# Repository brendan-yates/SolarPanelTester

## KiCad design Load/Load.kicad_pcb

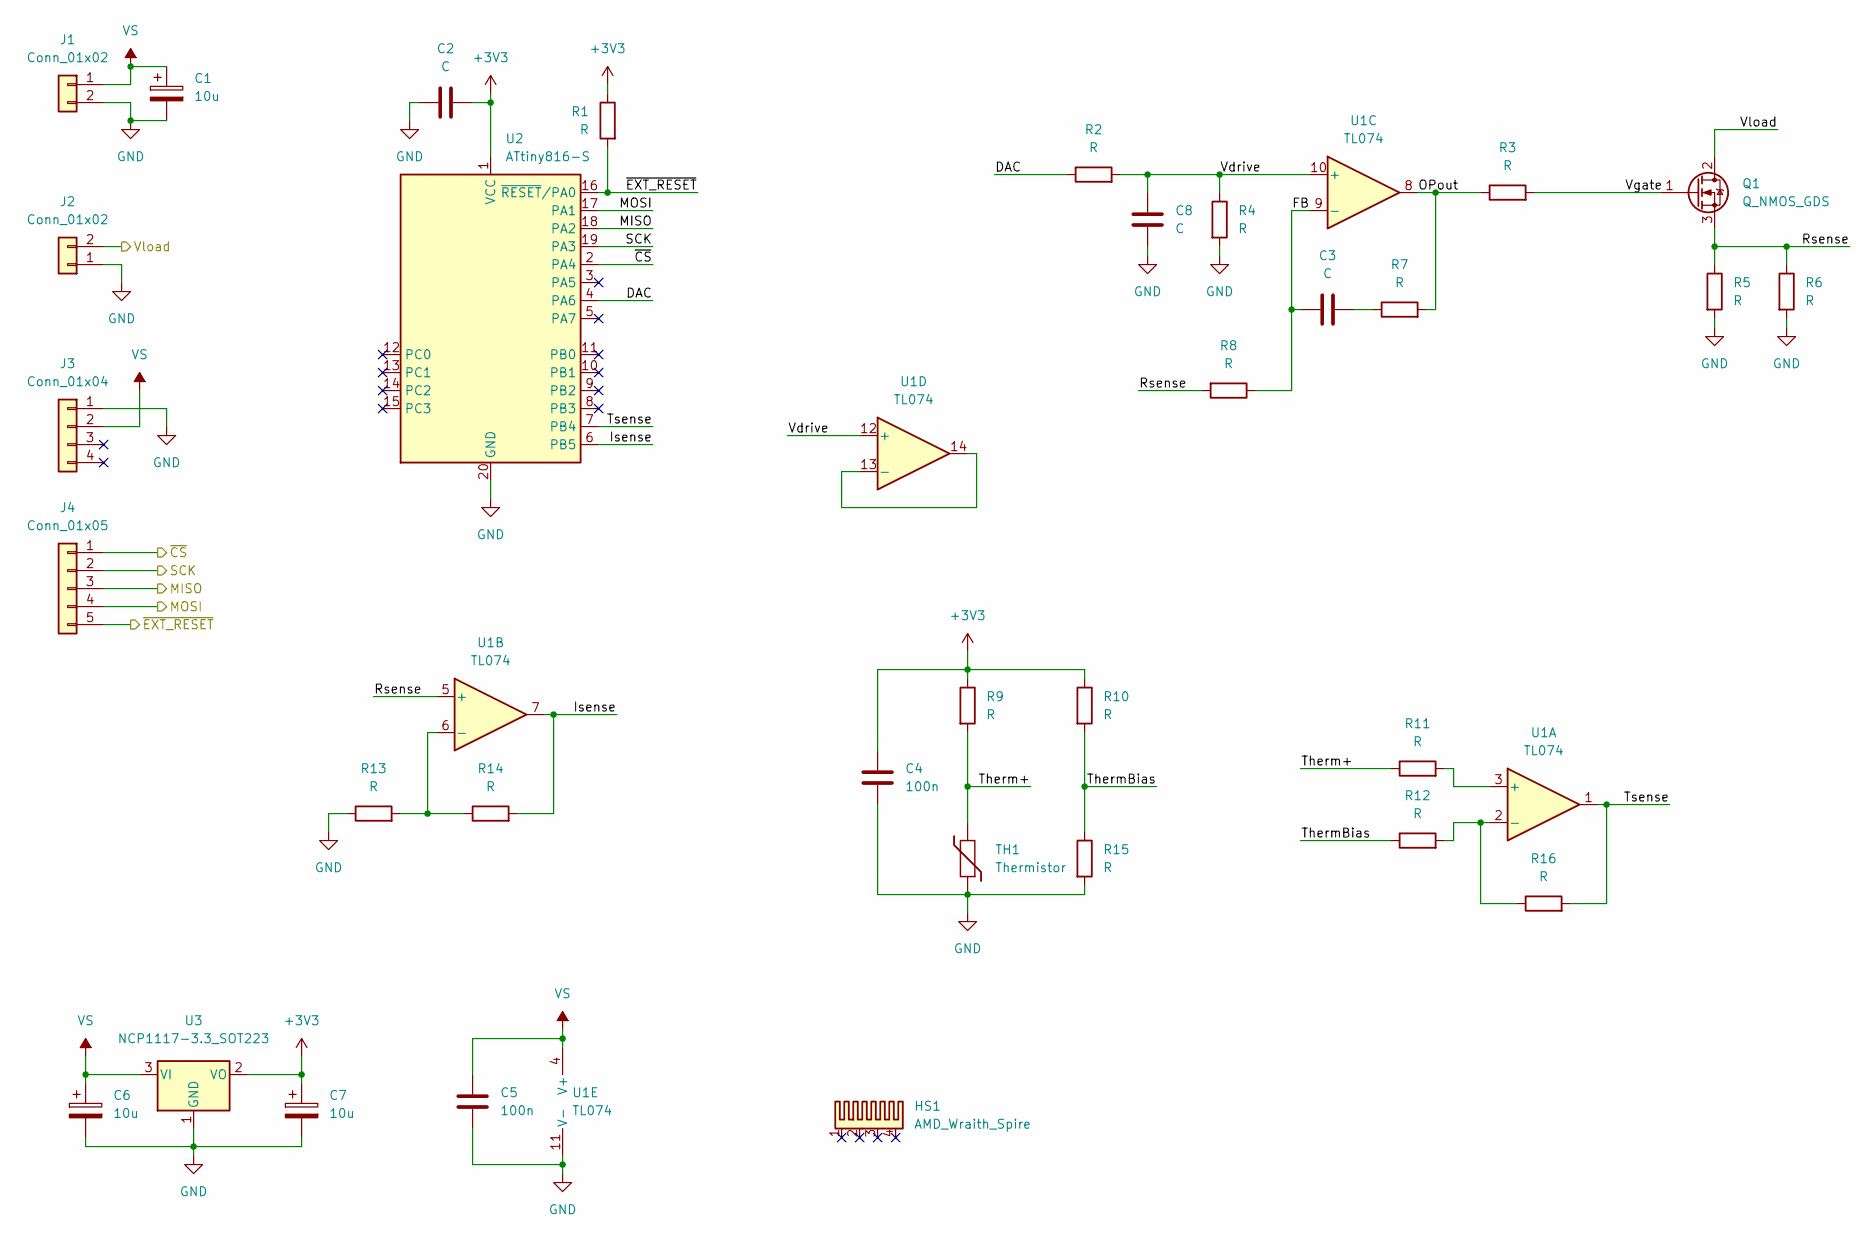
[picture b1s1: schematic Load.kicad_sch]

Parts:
C1, C6, C7: 10u; CP_EIA-3216-10_Kemet-I_Pad1.58x1.35mm_HandSolder
C2, C3, C8: C; C_0805_2012Metric_Pad1.18x1.45mm_HandSolder
C4, C5: 100n; C_0805_2012Metric_Pad1.18x1.45mm_HandSolder
HS1: AMD_Wraith_Spire
J1: Conn_01x02; PinSocket_1x02_P2.54mm_Vertical
J2: Conn_01x02; SolderWire-1sqmm_1x02_P5.4mm_D1.4mm_OD2.7mm_Relief
J3: Conn_01x04; PinSocket_1x04_P2.54mm_Vertical
J4: Conn_01x05; PinHeader_1x05_P2.54mm_Horizontal
Q1: Q_NMOS_GDS; TO-268-2
R1, R2, R3, R4, R7, R8, R9, R10, R11, R12, R13, R14, R15, R16: R; R_0805_2012Metric_Pad1.20x1.40mm_HandSolder
R5, R6: R; R_2512_6332Metric_Pad1.40x3.35mm_HandSolder
TH1: Thermistor; PinHeader_1x02_P2.54mm_Horizontal
U1: TL074; SOIC-14_3.9x8.7mm_P1.27mm
U2: ATtiny816-S; SOIC-20W_7.5x12.8mm_P1.27mm
U3: NCP1117-3.3_SOT223; SOT-223-3_TabPin2

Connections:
+3V3: C2.2, C4.2, C7.1, R1.1, R9.1, R10.1, U2.1 (VCC), U3.2 (VO)
/DAC: R2.1, U2.4 (PA6)
/FB: C3.1, R8.1, U1.9 (-)
/Isense: R14.2, U1.7, U2.6 (PB5)
/MISO: J4.3, U2.18 (PA2)
/MOSI: J4.4, U2.17 (PA1)
/OPout: R3.1, R7.2, U1.8
/Rsense: Q1.3 (S), R5.1, R6.1, R8.2, U1.5 (+)
/SCK: J4.2, U2.19 (PA3)
/Therm+: R9.2, R11.1, TH1.2
/ThermBias: R10.2, R12.1, R15.1
/Tsense: R16.2, U1.1, U2.7 (PB4)
/Vdrive: C8.2, R2.2, R4.1, U1.10 (+), U1.12 (+)
/Vgate: Q1.1 (G), R3.2
/Vload: J2.2, Q1.2 (D)
/~CS: J4.1, U2.2 (PA4)
/~EXT_RESET: J4.5, R1.2, U2.16 (~RESET/PA0)
GND: C1.2, C2.1, C4.1, C5.1, C6.2, C7.2, C8.1, J1.2, J2.1, J3.1, R4.2, R5.2, R6.2, R13.1, R15.2, TH1.1, U1.11 (V-), U2.20 (GND), U3.1 (GND)
unnamed: C3.2, R7.1
unnamed: R11.2, U1.3 (+)
unnamed: R12.2, R16.1, U1.2 (-)
unnamed: R13.2, R14.1, U1.6 (-)
unnamed: U1.13 (-), U1.14
VS: C1.1, C5.2, C6.1, J1.1, J3.2, U1.4 (V+), U3.3 (VI)

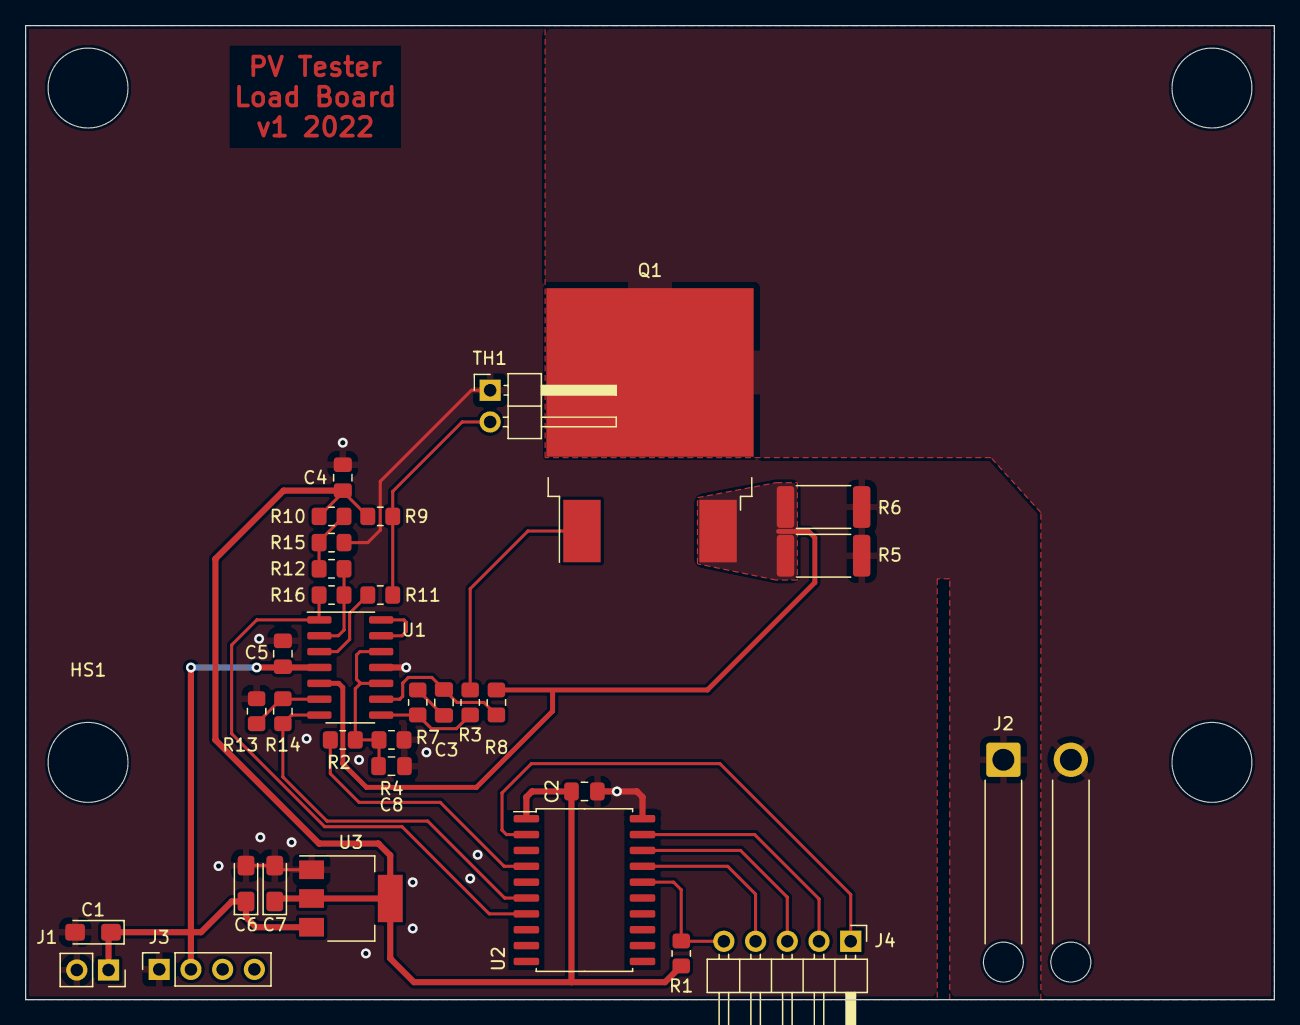
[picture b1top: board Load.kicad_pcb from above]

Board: 2 copper layers, 100.0 x 78.0 mm, 34 parts (0 on the bottom side), 24 nets.

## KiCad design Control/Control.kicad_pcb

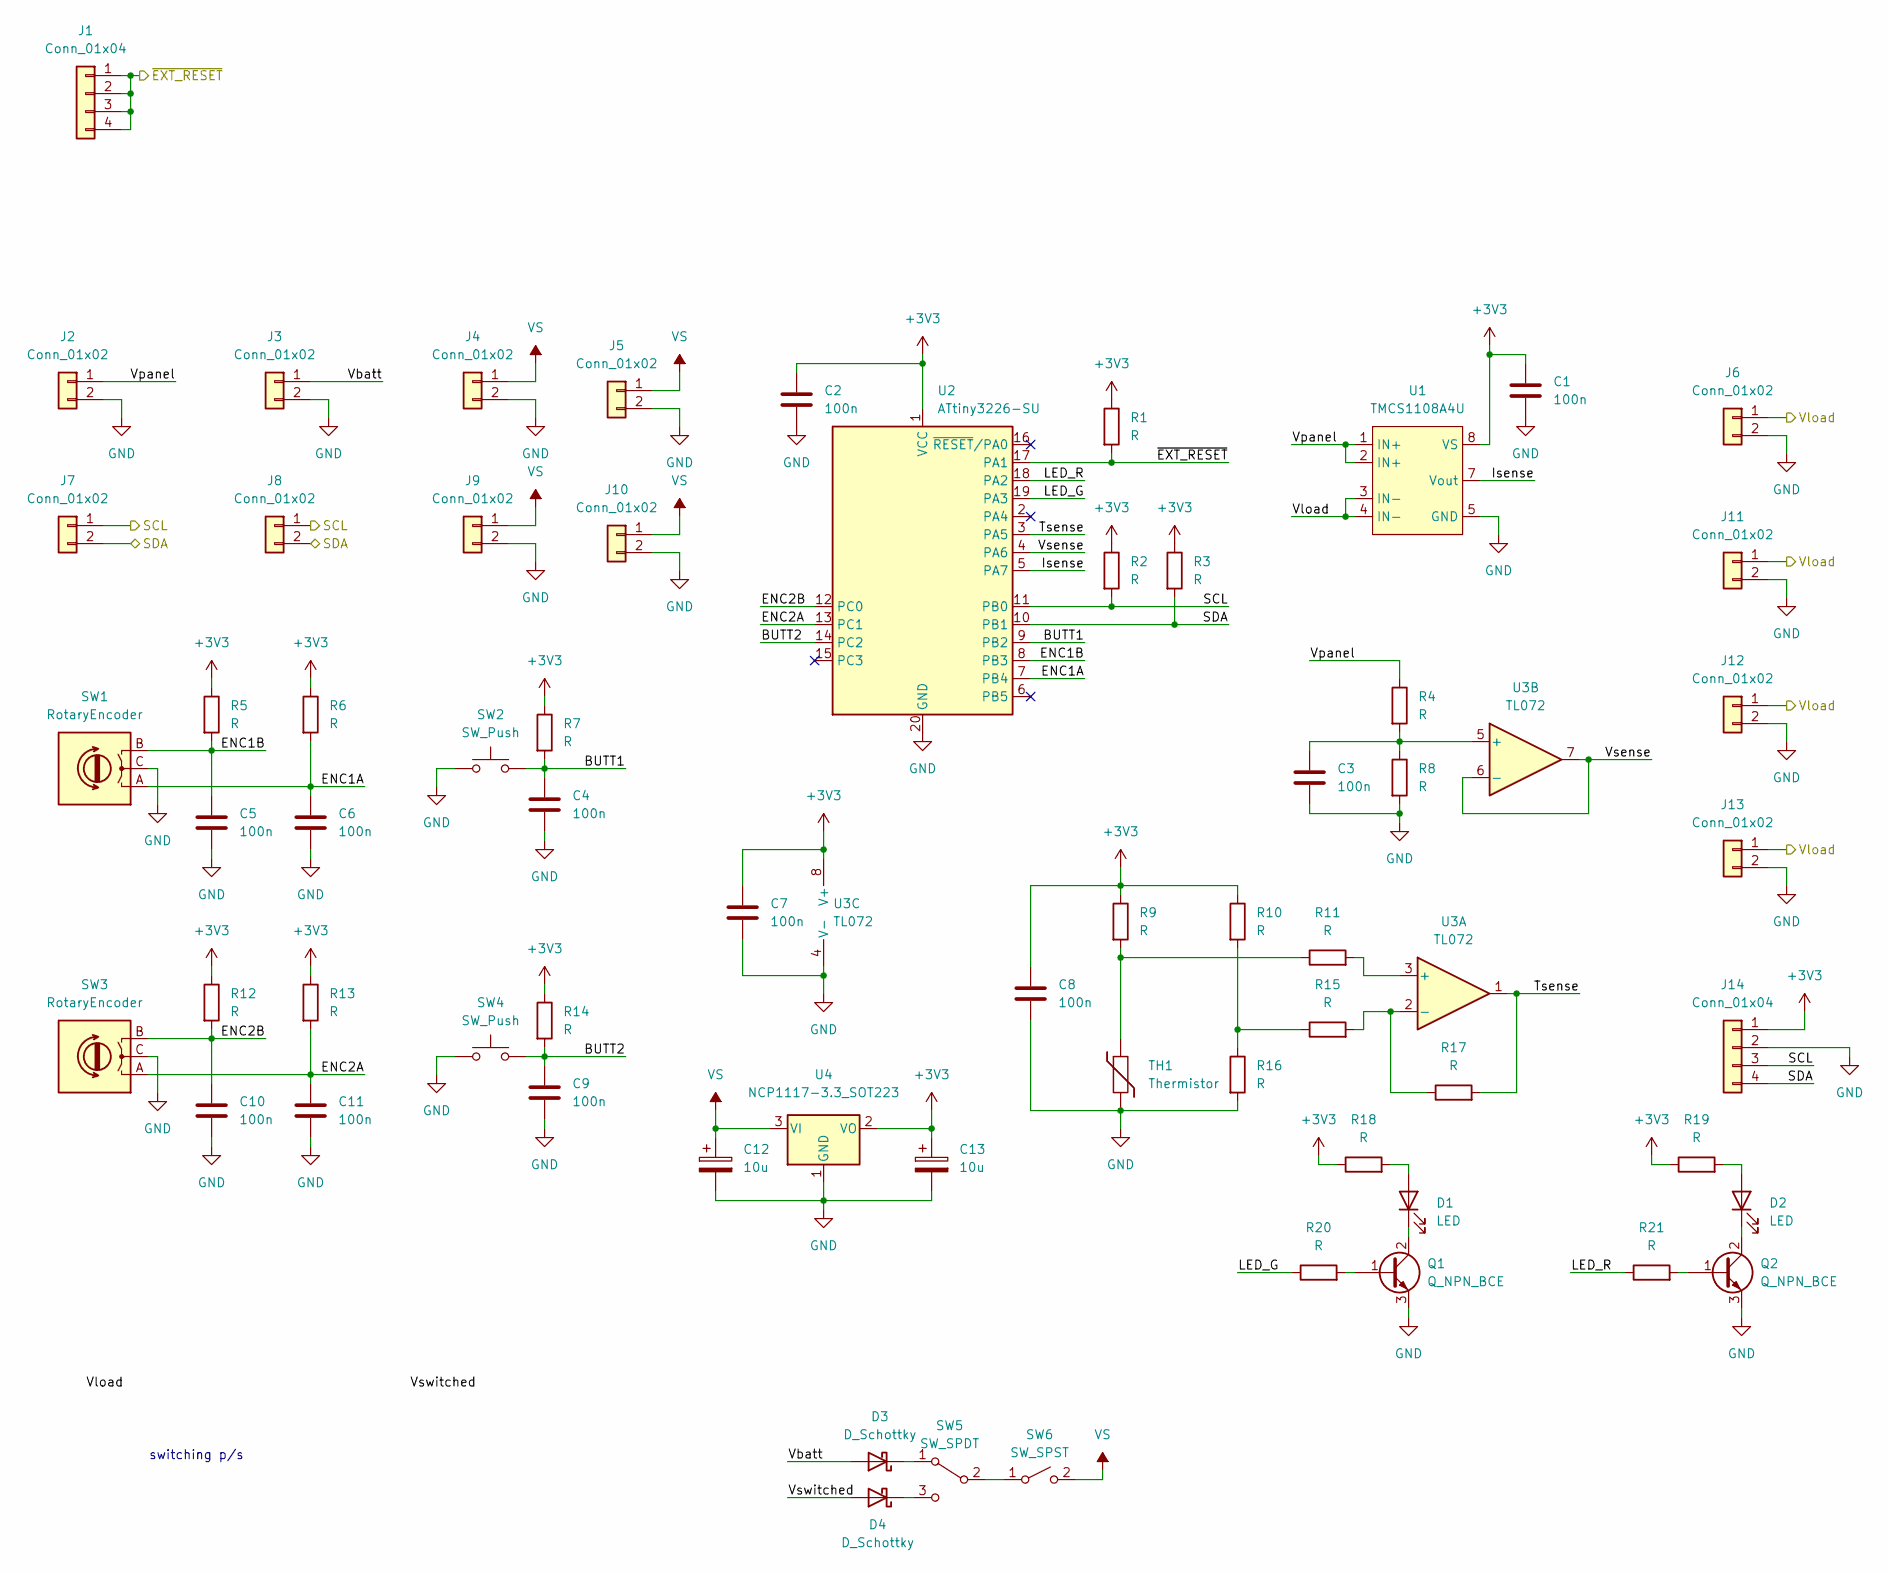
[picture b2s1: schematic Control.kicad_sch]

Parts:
C1, C2, C3, C4, C5, C6, C7, C8, C9, C10, C11: 100n; C_0805_2012Metric_Pad1.18x1.45mm_HandSolder
C12, C13: 10u; CP_EIA-3216-10_Kemet-I_Pad1.58x1.35mm_HandSolder
D1, D2: LED; PinSocket_1x02_P2.54mm_Vertical
D3, D4: D_Schottky; D_0805_2012Metric_Pad1.15x1.40mm_HandSolder
J1, J14: Conn_01x04; PinSocket_1x04_P2.54mm_Vertical
J2, J3, J4, J5, J6, J7, J8, J9, J10, J11, J12, J13: Conn_01x02; PinSocket_1x02_P2.54mm_Vertical
Q1, Q2: Q_NPN_BCE; SOT-23
R1, R2, R3, R4, R5, R6, R7, R8, R9, R10, R11, R12, R13, R14, R15, R16, R17, R18, R19, R20, R21: R; R_0805_2012Metric_Pad1.20x1.40mm_HandSolder
SW1, SW3: RotaryEncoder; RotaryEncoder_Alps_EC12E_Vertical_H20mm
SW2, SW4: SW_Push; PinSocket_1x02_P2.54mm_Vertical
SW5: SW_SPDT; PinSocket_1x03_P2.54mm_Vertical
SW6: SW_SPST; PinSocket_1x02_P2.54mm_Vertical
TH1: Thermistor; R_0805_2012Metric_Pad1.20x1.40mm_HandSolder
U1: TMCS1108A4U; SOIC-8_3.9x4.9mm_P1.27mm
U2: ATtiny3226-SU; SOIC-20W_7.5x12.8mm_P1.27mm
U3: TL072; SOIC-8_3.9x4.9mm_P1.27mm
U4: NCP1117-3.3_SOT223; SOT-223-3_TabPin2

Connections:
+3V3: C1.1, C2.1, C7.1, C8.2, C13.1, J14.1, R1.1, R2.1, R3.1, R5.1, R6.1, R7.1, R9.1, R10.1, R12.1, R13.1, R14.1, R18.1, R19.1, U1.8 (VS), U2.1 (VCC), U3.8 (V+), U4.2 (VO)
/BUTT1: C4.1, R7.2, SW2.2, U2.9 (PB2)
/BUTT2: C9.1, R14.2, SW4.2, U2.14 (PC2)
/ENC1A: C6.1, R6.2, SW1.A, U2.7 (PB4)
/ENC1B: C5.1, R5.2, SW1.B, U2.8 (PB3)
/ENC2A: C11.1, R13.2, SW3.A, U2.13 (PC1)
/ENC2B: C10.1, R12.2, SW3.B, U2.12 (PC0)
/Isense: U1.7 (Vout), U2.5 (PA7)
/LED_G: R20.1, U2.19 (PA3)
/LED_R: R21.1, U2.18 (PA2)
/SCL: J7.1, J8.1, J14.3, R2.2, U2.11 (PB0)
/SDA: J7.2, J8.2, J14.4, R3.2, U2.10 (PB1)
/Tsense: R17.2, U2.3 (PA5), U3.1
/Vbatt: D3.2 (A), J3.1
/Vload: J6.1, J11.1, J12.1, J13.1, U1.3 (IN-), U1.4 (IN-)
/Vpanel: J2.1, R4.1, U1.1 (IN+), U1.2 (IN+)
/Vsense: U2.4 (PA6), U3.6 (-), U3.7
/Vswitched: D4.2 (A)
/~EXT_RESET: J1.1, J1.2, J1.3, J1.4, R1.2, U2.17 (PA1)
GND: C1.2, C2.2, C3.2, C4.2, C5.2, C6.2, C7.2, C8.1, C9.2, C10.2, C11.2, C12.2, C13.2, J2.2, J3.2, J4.2, J5.2, J6.2, J9.2, J10.2, J11.2, J12.2, J13.2, J14.2, Q1.3 (E), Q2.3 (E), R8.2, R16.2, SW1.C, SW2.1, SW3.C, SW4.1, TH1.2, U1.5 (GND), U2.20 (GND), U3.4 (V-), U4.1 (GND)
unnamed: C3.1, R4.2, R8.1, U3.5 (+)
unnamed: D1.1 (K), Q1.2 (C)
unnamed: D1.2 (A), R18.2
unnamed: D2.1 (K), Q2.2 (C)
unnamed: D2.2 (A), R19.2
unnamed: D3.1 (K), SW5.1 (A)
unnamed: D4.1 (K), SW5.3 (C)
unnamed: Q1.1 (B), R20.2
unnamed: Q2.1 (B), R21.2
unnamed: R10.2, R15.1, R16.1
unnamed: R9.2, R11.1, TH1.1
unnamed: R11.2, U3.3 (+)
unnamed: R15.2, R17.1, U3.2 (-)
unnamed: SW5.2 (B), SW6.1 (A)
VS: C12.1, J4.1, J5.1, J9.1, J10.1, SW6.2 (B), U4.3 (VI)

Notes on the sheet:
switching p/s

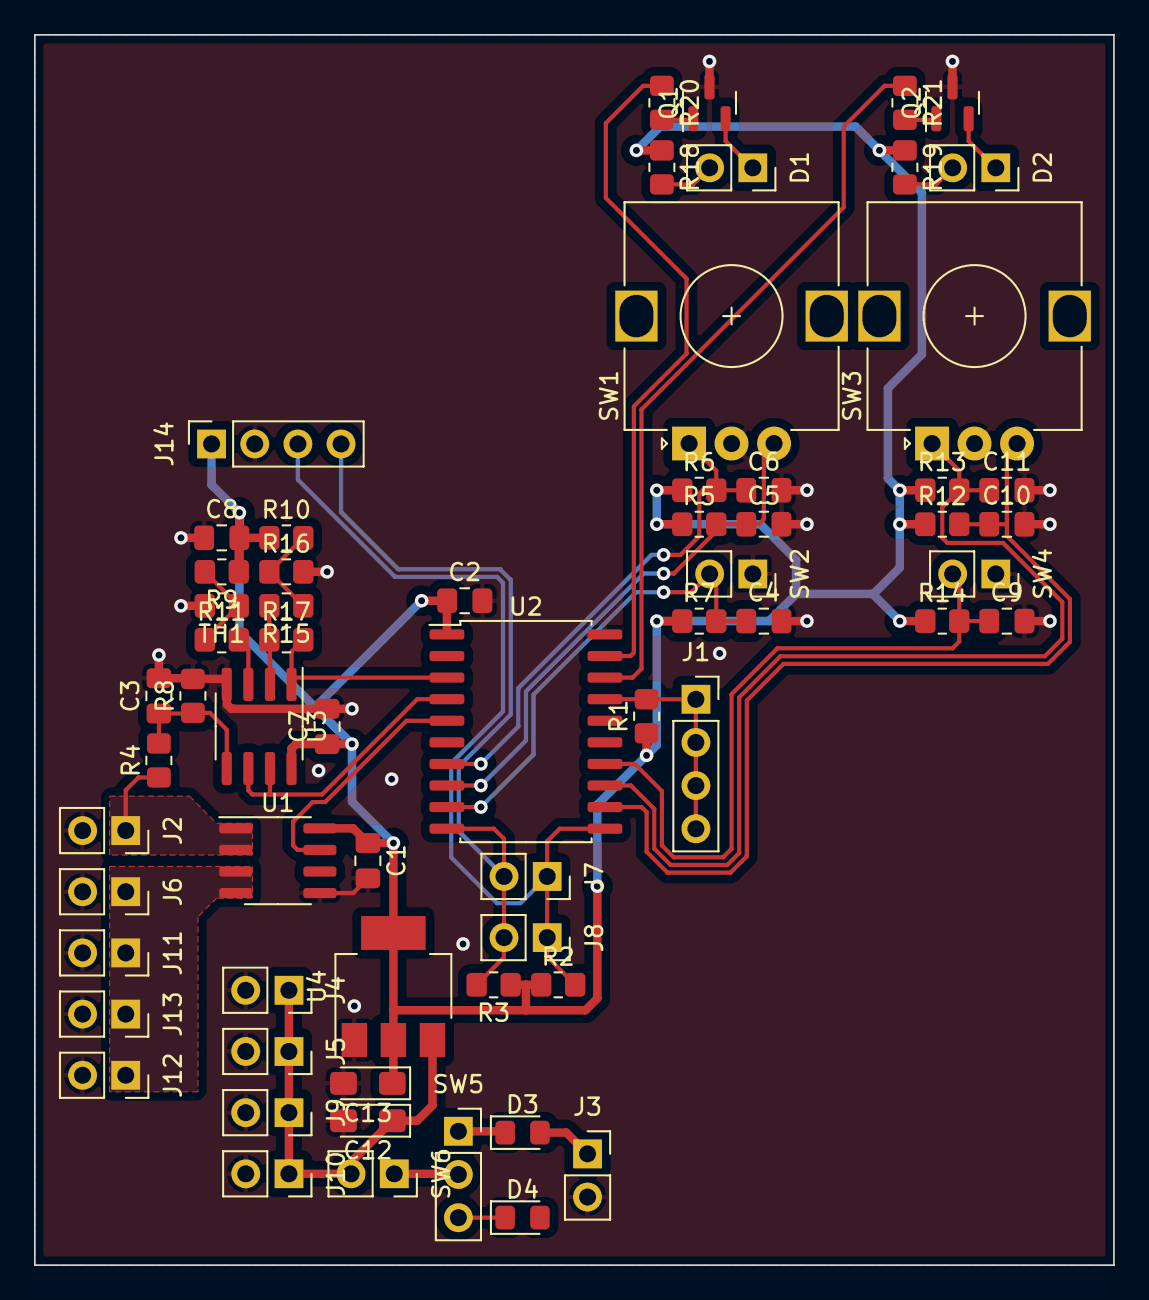
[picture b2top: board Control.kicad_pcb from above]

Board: 2 copper layers, 63.5 x 72.4 mm, 65 parts (0 on the bottom side), 34 nets.
